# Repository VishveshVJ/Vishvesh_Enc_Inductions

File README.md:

Basics : Question 1. This Question's File are in kratos_vishvesh folder

    Create a ROS2 Publihser Node. (Learnt How to Publish)
    How to import differnt data types from other packages
    Create a ROS2 Subscriber Node.
    Biggest Challenge was installing python files in c++ package

Question 2 : This Questions Files are in kratos_vishvesh_q2 and the custom msg is in kratos_vishvesh_q2-msgs

    Learning how to create a custom msg
    Crearting the publishers and subscriber nodes with 2 Hz freq
    Verify the message received
    Biggest Challenge was learning about making a custom msg folder and installing / adding dependencies to the kratos_vishvesh_q2 package

IKFK : Question 1 : Uploaded

Question 2: File : kratos_inductions

    Understaing the Kinematics of the acutall robot by sending message with set angles.
    Studying the urdf file to knowing the dimensions
    Calculating the range and doing the fkik calc
    setting up the nodes
    Challenges Faced : Aanalyzing the urdf file and calc ikfk
    Testing Unreachable positions
    Bugs - It does not take collision into perspective

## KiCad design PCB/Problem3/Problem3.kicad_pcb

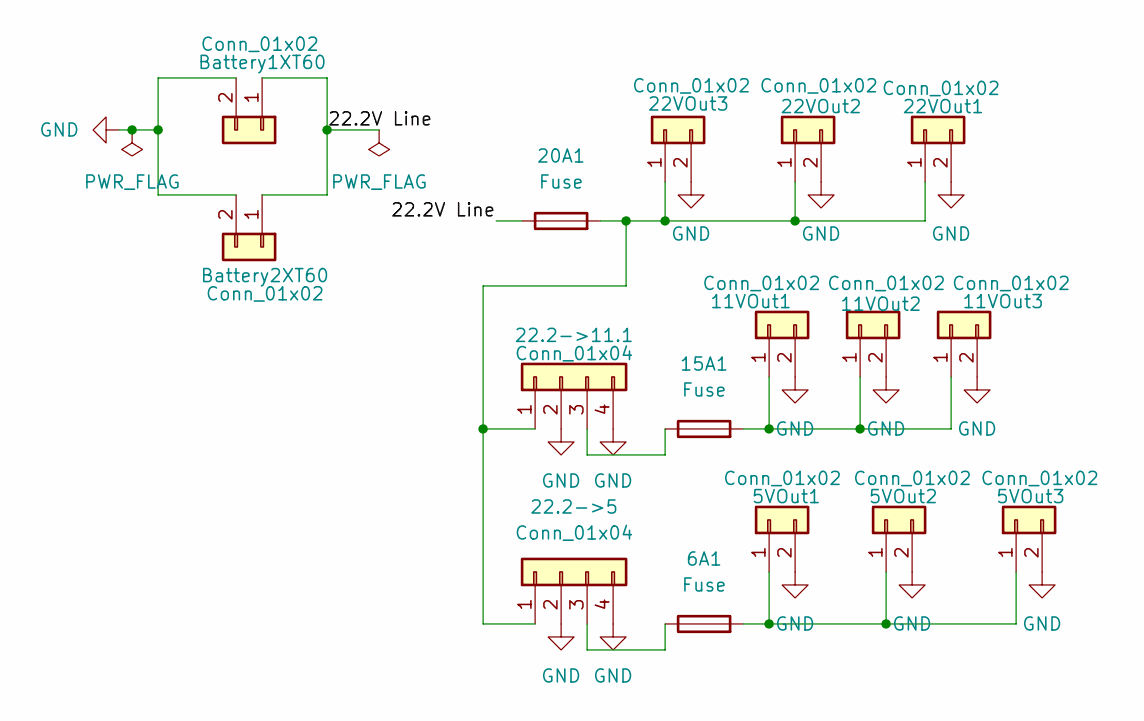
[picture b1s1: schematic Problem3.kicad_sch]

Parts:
5VOut1, 5VOut2, 5VOut3: Conn_01x02; PinHeader_1x02_P2.54mm_Vertical
6A1, 15A1, 20A1: Fuse; Fuseholder_Cylinder-5x20mm_Schurter_0031_8201_Horizontal_Op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
11VOut1, 11VOut2, 11VOut3, 22VOut1, 22VOut2, 22VOut3: Conn_01x02; AMASS_XT60-F_1x02_P7.20mm_Vertical
22.2->5, 22.2->11.1: Conn_01x04; PinHeader_1x04_P2.54mm_Vertical
Battery1XT60, Battery2XT60: Conn_01x02; AMASS_XT60-F_1x02_P7.20mm_Vertical

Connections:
/22.2V Line: 20A1.1, Battery1XT60.1, Battery2XT60.1
GND: 5VOut1.2, 5VOut2.2, 5VOut3.2, 11VOut1.2, 11VOut2.2, 11VOut3.2, 22.2->5.2, 22.2->5.4, 22.2->11.1.2, 22.2->11.1.4, 22VOut1.2, 22VOut2.2, 22VOut3.2, Battery1XT60.2, Battery2XT60.2
unnamed: 5VOut1.1, 5VOut2.1, 5VOut3.1, 6A1.2
unnamed: 11VOut1.1, 11VOut2.1, 11VOut3.1, 15A1.2
unnamed: 6A1.1, 22.2->5.3
unnamed: 20A1.2, 22.2->5.1, 22.2->11.1.1, 22VOut1.1, 22VOut2.1, 22VOut3.1
unnamed: 15A1.1, 22.2->11.1.3

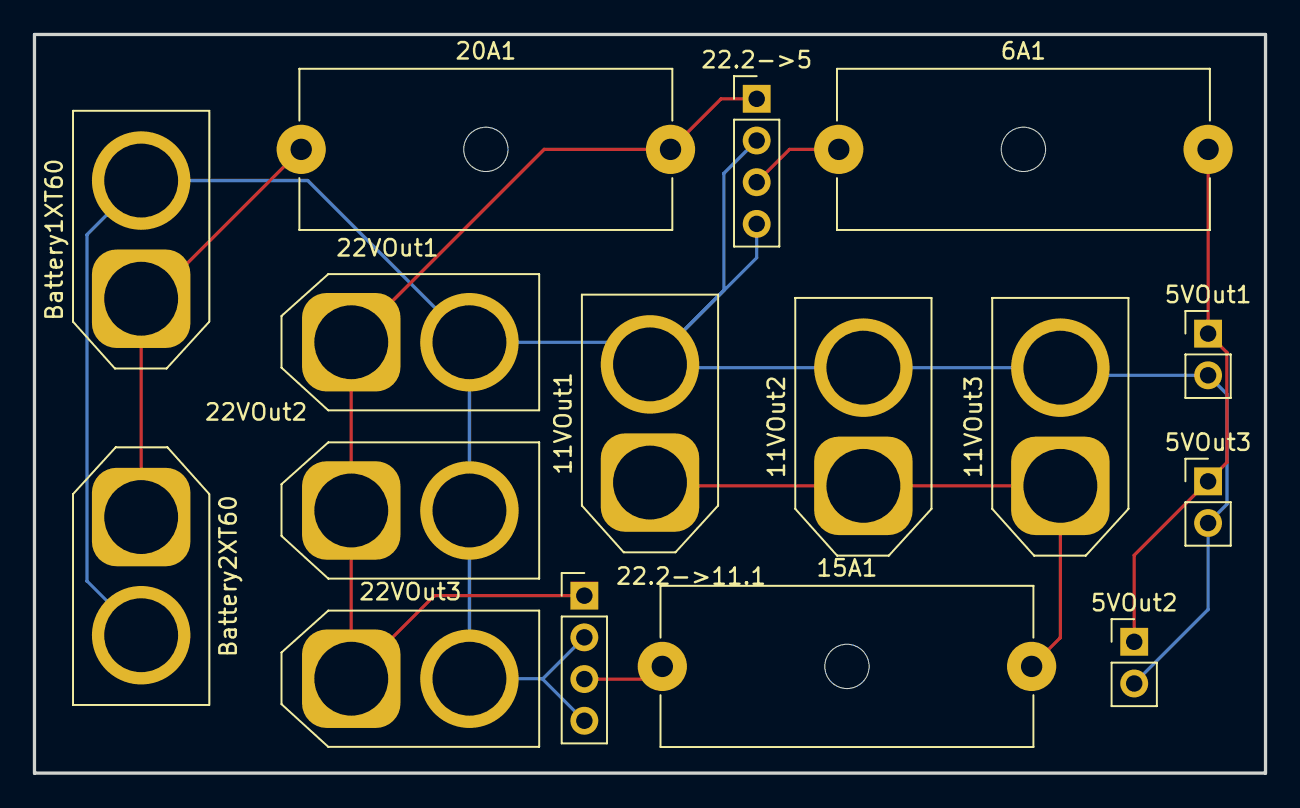
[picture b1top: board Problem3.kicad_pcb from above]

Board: 2 copper layers, 75.0 x 45.0 mm, 16 parts (0 on the bottom side), 7 nets.

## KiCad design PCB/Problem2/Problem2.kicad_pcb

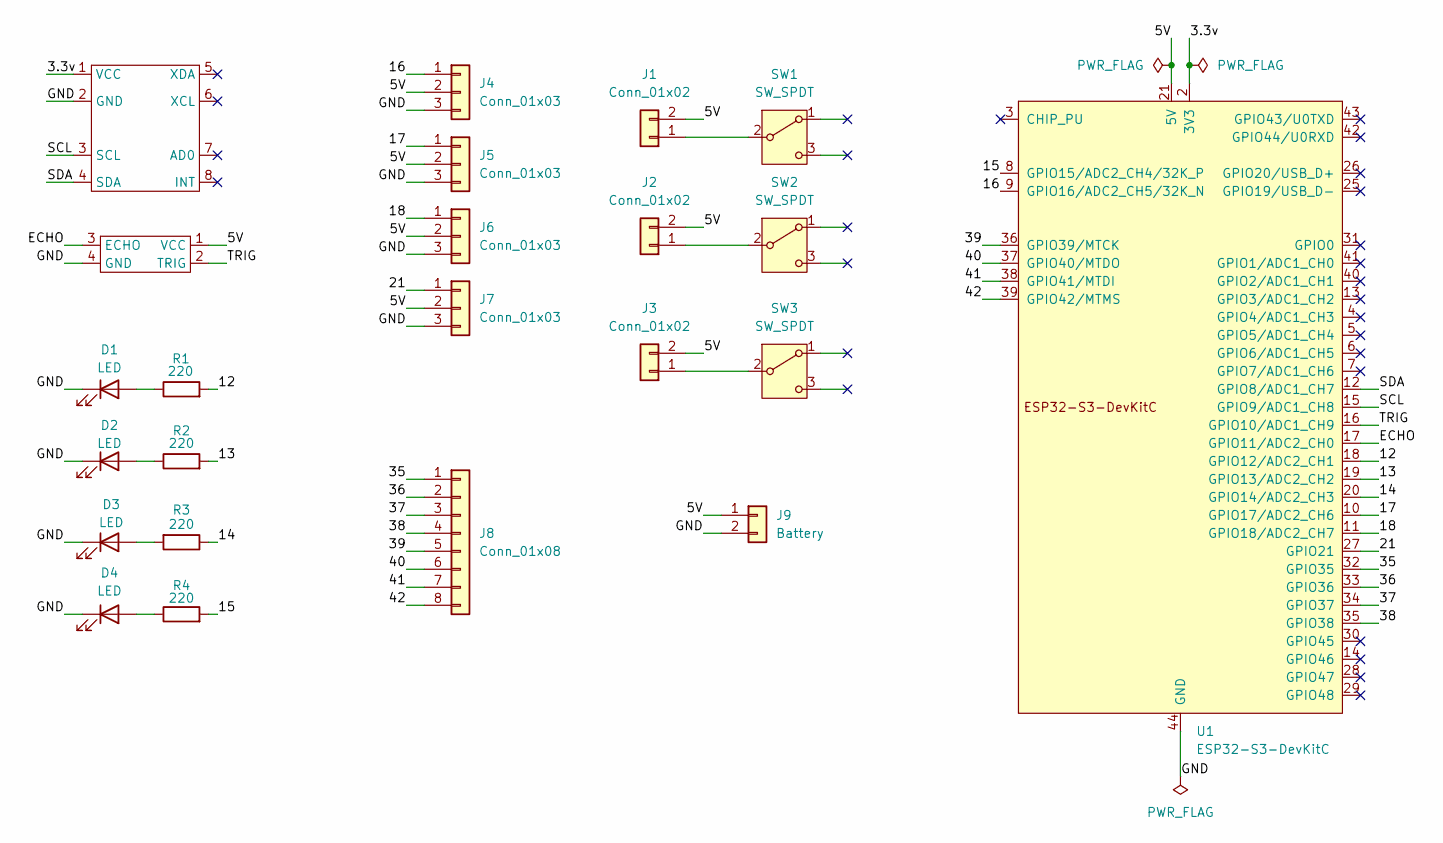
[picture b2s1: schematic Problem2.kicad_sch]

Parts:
D1, D2, D3, D4: LED; LED_D5.0mm
J1, J2, J3: Conn_01x02; PinHeader_1x02_P2.54mm_Vertical
J4, J5, J6, J7: Conn_01x03; PinHeader_1x03_P2.54mm_Vertical
J8: Conn_01x08; PinHeader_1x08_P2.54mm_Vertical
J9: Battery; TerminalBlock_MaiXu_MX126-5.0-02P_1x02_P5.00mm
R1, R2, R3, R4: 220; R_Axial_DIN0207_L6.3mm_D2.5mm_P7.62mm_Horizontal
SW1, SW2, SW3: SW_SPDT; SW_CK_JS202011AQN_DPDT_Angled
U1: ESP32-S3-DevKitC
U2: MPU6050_Module
U3: XCVR_HC-SR04

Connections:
/3.3v: U1.1 (3V3), U1.2 (3V3), U2.1 (VCC)
/5V: J1.2, J2.2, J3.2, J4.2, J5.2, J6.2, J7.2, J9.1, U1.21 (5V), U3.1 (VCC)
/12: R1.2, U1.18 (GPIO12/ADC2_CH1)
/13: R2.2, U1.19 (GPIO13/ADC2_CH2)
/14: R3.1, U1.20 (GPIO14/ADC2_CH3)
/15: R4.2, U1.8 (GPIO15/ADC2_CH4/32K_P)
/16: J4.1, U1.9 (GPIO16/ADC2_CH5/32K_N)
/17: J5.1, U1.10 (GPIO17/ADC2_CH6)
/18: J6.1, U1.11 (GPIO18/ADC2_CH7)
/21: J7.1, U1.27 (GPIO21)
/35: J8.1, U1.32 (GPIO35)
/36: J8.2, U1.33 (GPIO36)
/37: J8.3, U1.34 (GPIO37)
/38: J8.4, U1.35 (GPIO38)
/39: J8.5, U1.36 (GPIO39/MTCK)
/40: J8.6, U1.37 (GPIO40/MTDO)
/41: J8.7, U1.38 (GPIO41/MTDI)
/42: J8.8, U1.39 (GPIO42/MTMS)
/ECHO: U1.17 (GPIO11/ADC2_CH0), U3.3 (ECHO)
/GND: D1.1 (K), D2.1 (K), D3.1 (K), D4.1 (K), J4.3, J5.3, J6.3, J7.3, J9.2, U1.22 (GND), U1.23 (GND), U1.24 (GND), U1.44 (GND), U2.2 (GND), U3.4 (GND)
/SCL: U1.15 (GPIO9/ADC1_CH8), U2.3 (SCL)
/SDA: U1.12 (GPIO8/ADC1_CH7), U2.4 (SDA)
/TRIG: U1.16 (GPIO10/ADC1_CH9), U3.2 (TRIG)
unnamed: D1.2 (A), R1.1
unnamed: D2.2 (A), R2.1
unnamed: D3.2 (A), R3.2
unnamed: D4.2 (A), R4.1
unnamed: J1.1, SW1.2 (B)
unnamed: J2.1, SW2.2 (B)
unnamed: J3.1, SW3.2 (B)

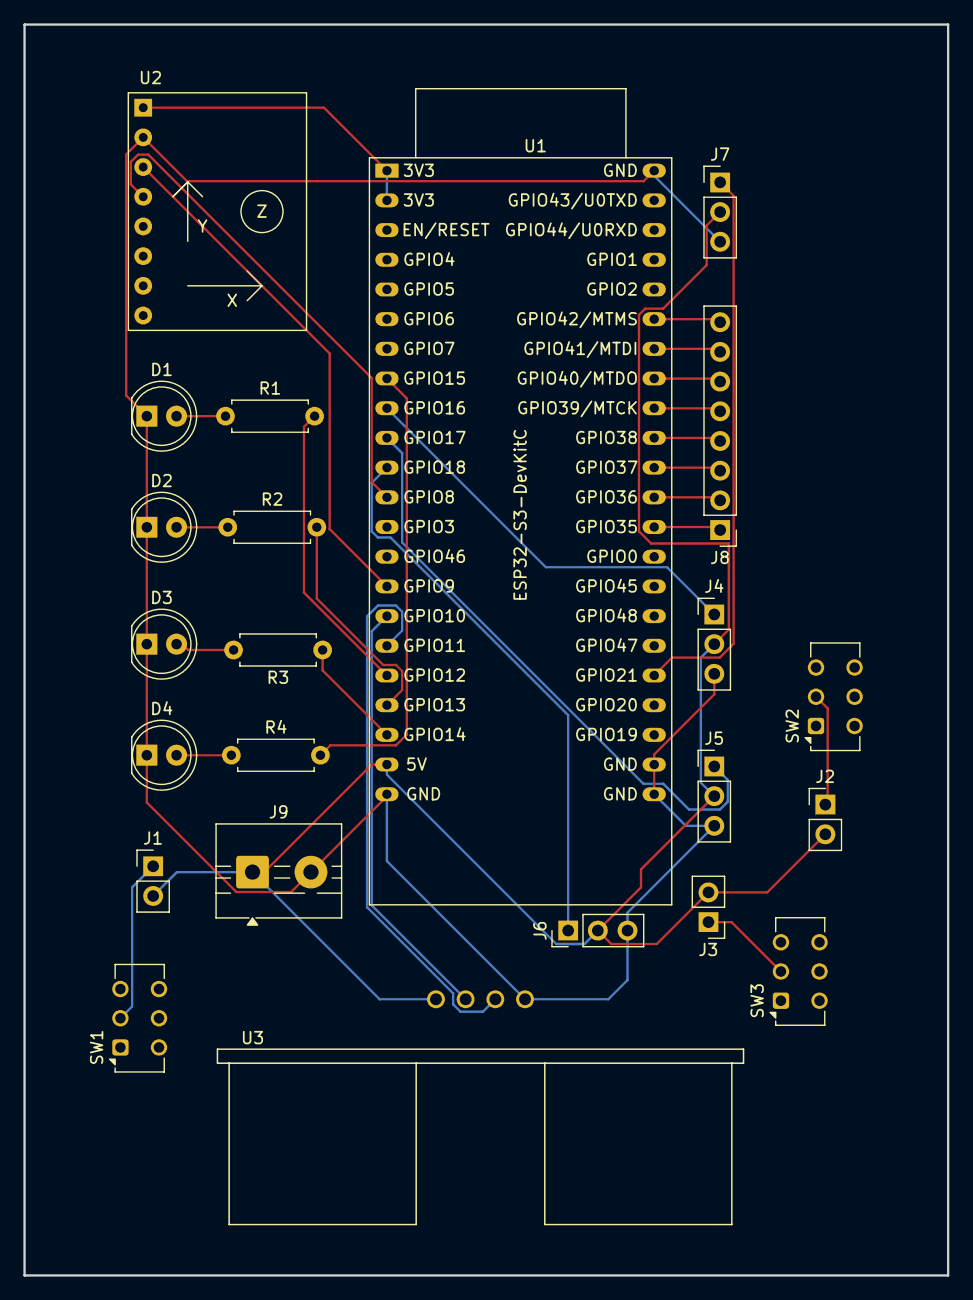
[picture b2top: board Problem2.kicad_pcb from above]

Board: 2 copper layers, 79.0 x 107.0 mm, 23 parts (0 on the bottom side), 30 nets.
